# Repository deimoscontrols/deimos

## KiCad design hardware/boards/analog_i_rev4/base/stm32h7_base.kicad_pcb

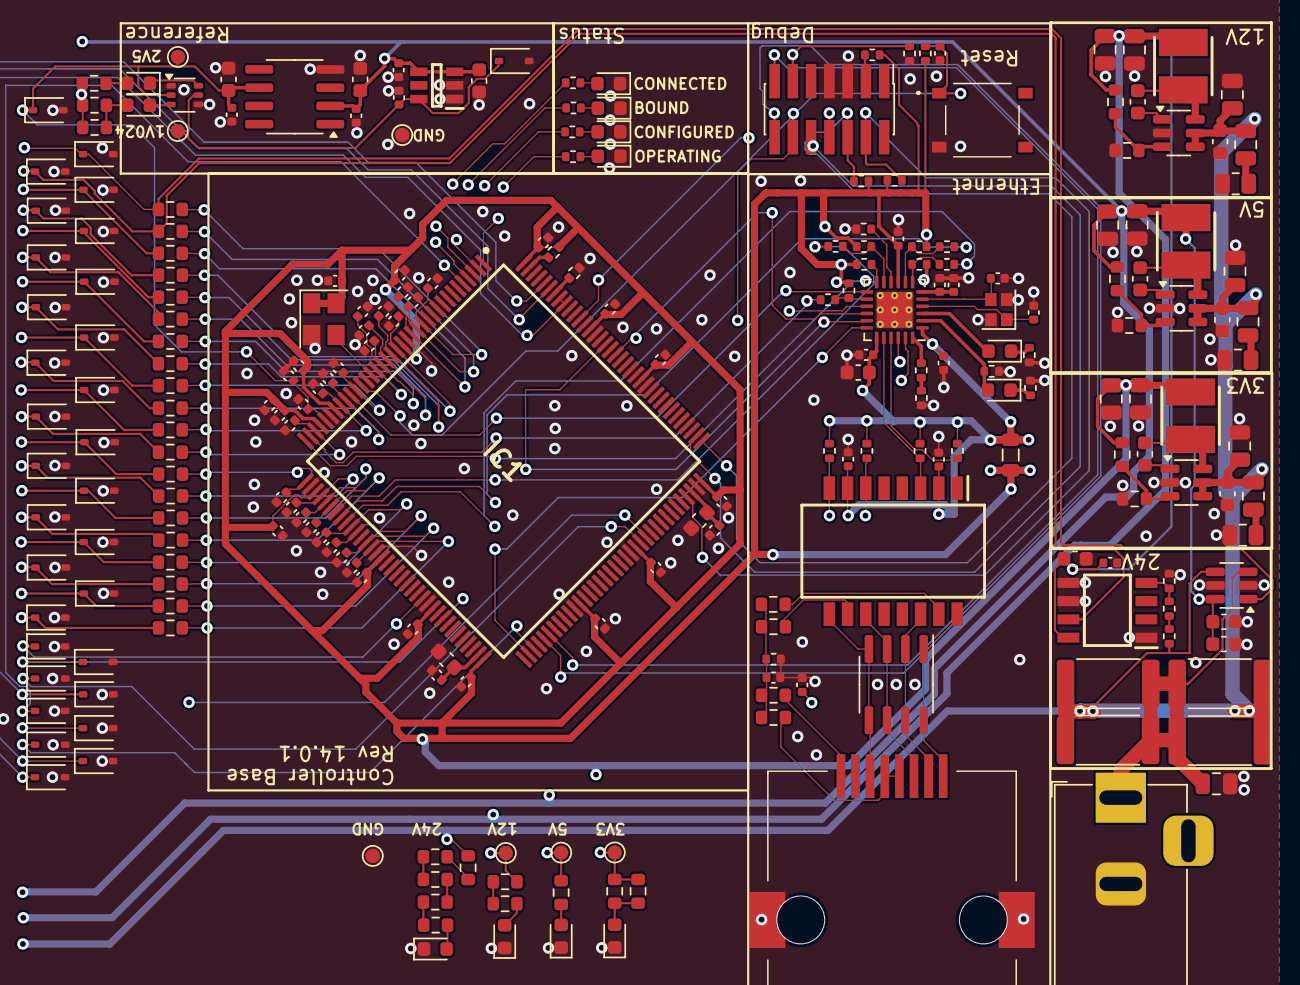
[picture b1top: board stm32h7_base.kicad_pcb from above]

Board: 4 copper layers, 242 parts (0 on the bottom side), 143 nets.

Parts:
C9, C10, C23, C4005, C5002, C5004, C6003: 10uF; C_0603_1608Metric
C11, C12, C13, C14, C15, C17, C18, C19, C22, C24, C26, C28, C29, C30, C31, C32, C33, C34, C35, C36, C37, C38, C39, C40, C4004, C5001, C5003, C6001, C6002: 0.1uF; C_0402_1005Metric
C16: 4.7nF; C_0402_1005Metric
C20, C21: 5.6pF 0402; C_0402_1005Metric
C25: 470pF 0402; C_0402_1005Metric
C27, C44, C45, C46, C47, C48, C49, C50, C51, C52, C53, C54, C55, C56, C57, C58, C59, C60, C61, C62, C63: 1uF 0402; C_0402_1005Metric
C42, C43: 10nF; C_0402_1005Metric
C4001: 0.1uF 0603; C_0603_1608Metric
C4002: 10uF 0603; C_0603_1608Metric
C4003, C7001, C7002, C7004, C8003, C9004, C11005, C11006, C12002, C12003: 10uF 50V 0805; C_0805_2012Metric
C7003, C8001, C9001, C9002, C10005, C11009: 0.1uF 50V 0603; C_0603_1608Metric
C8002, C9003, C10006: 2.2uF 50V 0805; C_0805_2012Metric
D2, D6, D36, D37, D38, D39, D7004, D7005, D7006, D7007, D7008, D7009: Purple LED; LED_0603_1608Metric
D5: CDNBS08-SLVU2.8-4; SOIC-8_3.9x4.9mm_P1.27mm
D7, D1001, D1002, D1003, D1004, D1005, D1006, D1007, D1008, D1009, D1010, D1011, D1012, D1013, D1014, D1015, D1016, D1017, D1018, D1019, D1020, D1021, D1022, D1023, D1024, D1025, D1026, D1027, D1028, D1029, D1030: BZT52C5V6S; D_SOD-323
FB1: GZ2012D601TF; L_0805_2012Metric
H1001, H1002: MountingHole_for_10-32; MountingHole_5mm
IC1: STM32H743ZIT6; QFP50P2200X2200X160-144N
IC5004: REF35102QDBVR; SOT95P280X145-6N
IC8001: INA826AIDR; SOIC127P600X175-8N
IC8002, IC10001, IC12001: TPS560430XDBVR; SOT-23-6
J4: Conn_02x07_Odd_Even; PinHeader_2x07_P1.27mm_Vertical_SMD
J7: 6339160-1; 63391601
J8001: Barrel_Jack; BarrelJack_Horizontal
L7001: 12uH FNR4030S120MT; INDPM4040X300N
L9001: 33uH FNR4020S330MT; INDPM4040X300N
L11001: 18uH FNR4030S180MT; INDPM4040X300N
R1, R2, R3, R4, R5, R6, R27, R28, R29, R30, R31, R33, R49, R50, R53, R55, R8006, R8007: 10k; R_0402_1005Metric
R8, R9, R10, R11, R22, R32, R35, R36, R37, R38, R39, R40, R41, R42, R43, R44, R45, R46, R51, R52: 10R 0603; R_0603_1608Metric
R13, R14, R15, R16: 49.9; R_0402_1005Metric
R17, R18, R19, R20: 75; R_0603_1608Metric
R21: 1M; R_0402_1005Metric
R23, R26, R47, R48: 33R; R_0402_1005Metric
R34, R56, R8005: 1.5k; R_0402_1005Metric
R54: 12k; R_0402_1005Metric
R57: 100R; R_0402_1005Metric
R58, R2001: 100R 0402; R_0402_1005Metric
R4001, R4002, R4003, R8004: MRF6432(2512)LR030FTS 0.030 1%; R_2512_6332Metric
R7001: 51k 0603; R_0603_1608Metric
R7025, R7026, R7027, R7028, R7029, R7030, R7031, R7033, R7034, R10002, R10004, R10005, R10006: 10k; R_0603_1608Metric
R9001: 243k 0603; R_0603_1608Metric
R9002, R10001, R11004: 22.1k 0603; R_0603_1608Metric
R10003, R11005, R12003: 1R 0805; R_0805_2012Metric
R11003: 88.7k 0603; R_0603_1608Metric
S1: TS-1187A-B-A-B; TS1187ABAB
T1: H1102NLT; SOIC127P940X622-16N
TP4001: TestPoint_GND_1; TestPoint_Pad_D1.0mm
TP10001: TestPoint_+12V; TestPoint_Pad_D1.0mm
TP10002: TestPoint_+5V; TestPoint_Pad_D1.0mm
TP10003: TestPoint_+2V5; TestPoint_Pad_D1.0mm
TP10004: TestPoint_+3V3; TestPoint_Pad_D1.0mm
TP10005: TestPoint_+1V024; TestPoint_Pad_D1.0mm
TP10006: TestPoint_GND; TestPoint_Pad_D1.0mm
U5: LAN8742A; VQFN-24-1EP_4x4mm_P0.5mm_EP2.5x2.5mm_ThermalVias
U4001: INA181A2; SOT-23-6
U6002: ADR4525; SOIC-8_3.9x4.9mm_P1.27mm
U10001: NTJD4001NT1G; SOT-363_SC-70-6
Y1: SiT1602BI-21-33S-48.000000; Crystal_SMD_3225-4Pin_3.2x2.5mm
Y2: NX2016SA-25.000M-STD-CZS-1; Crystal_SMD_2016-4Pin_2.0x1.6mm

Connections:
+1V024: C6001.2, D1030.1 (K), IC5004.6 (VREF), TP10005.1, U10001.5 (G2)
+2V5: C28.2, C43.2, C5003.2, C5004.2, D1028.1 (K), IC1.32 (VREF+), TP10003.1, U6002.6 (OUT), U10001.2 (G1)
+3V3: C11.2, C12.2, C26.2, C29.2, C30.2, C31.2, C32.2, C33.2, C34.2, C35.2, C36.2, C37.2, C38.2, C39.2, C40.2, C42.2, C7004.1, C10006.1, FB1.1, IC1.17 (VDD_1), IC1.30 (VDD_2), IC1.33 (VDDA), IC1.39 (VDD_3), IC1.52 (VDD_4), IC1.62 (VDD_5), IC1.72 (VDD_6), IC1.84 (VDD_7), IC1.95 (VDD33USB), IC1.108 (VDD_8), IC1.121 (VDD_9), IC1.131 (VDD_10), IC1.144 (VDD_11), L7001.1, R1.2, R2.1, R3.2, R6.1, R27.1, R28.1, R29.1, R49.1, R56.2, R2001.1, R7001.1, R7031.2, R10002.2, TP10004.1, U5.9 (VDDIO), Y1.1 (OE/~ST/NC), Y1.4 (VDD)
+5V: C4001.1, C4002.1, C5001.2, C5002.2, C6002.2, C6003.2, C8002.1, C8003.1, IC5004.3 (EN), IC5004.4 (VIN), L11001.1, R7029.2, R7030.2, R10004.2, R10005.2, R11003.1, TP10002.1, U4001.6 (V+), U6002.2 (IN)
+12V: C4004.2, C4005.2, C9003.1, C9004.1, IC8001.8 (+VS), L9001.1, R7027.2, R9001.1, TP10001.1
+24V: C7001.1, C7002.1, C8001.1, C9001.1, C10005.1, C11005.1, C11006.1, C12002.1, C12003.1, IC8002.4 (EN), IC8002.5 (VIN), IC10001.4 (EN), IC10001.5 (VIN), IC12001.4 (EN), IC12001.5 (VIN), R4001.1, R4002.1, R4003.1, R8004.1, R8006.1, R10006.2, U4001.4 (-)
/AIN0: D7.1 (K), R8.1, U4001.1
/AIN1: D1001.1 (K), IC8001.7 (VOUT), R9.1
/AIN2: D1002.1 (K), R10.1
/AIN3: D1003.1 (K), R11.1
/AIN4: D1004.1 (K), R22.1
/AIN5: D1005.1 (K), R32.1
/AIN6: D1006.1 (K), R35.1
/AIN7: D1007.1 (K), R36.1
/AIN8: D1008.1 (K), R37.1
/AIN9: D1009.1 (K), R38.1
/AIN10: D1010.1 (K), R39.1
/AIN11: D1011.1 (K), R40.1
/AIN12: D1012.1 (K), R41.1
/AIN13: D1013.1 (K), R42.1
/AIN14: D1014.1 (K), R43.1
/AIN15: D1015.1 (K), R44.1
/AIN16: D1016.1 (K), R45.1
/AIN17: D1017.1 (K), R46.1
/AIN18: D1018.1 (K), R51.1
/AIN19: D1019.1 (K), R52.1
/COUNTER0: D1025.1 (K), IC1.96 (PC6)
/ENCODER0_0: D1020.1 (K), IC1.60 (PE9)
/ENCODER0_1: D1029.1 (K), IC1.64 (PE11)
/FREQ0: D1026.1 (K), IC1.136 (PB6), IC1.137 (PB7)
/FREQ1: D1027.1 (K), IC1.5 (PE6)
/Micro/AIN0_Filt: C44.1, IC1.13 (PF3), R8.2
/Micro/AIN1_Filt: C45.1, IC1.14 (PF4), R9.2
/Micro/AIN2_Filt: C46.1, IC1.15 (PF5), R10.2
/Micro/AIN3_Filt: C47.1, IC1.18 (PF6), R11.2
/Micro/AIN4_Filt: C48.1, IC1.19 (PF7), R22.2
/Micro/AIN5_Filt: C49.1, IC1.20 (PF8), R32.2
/Micro/AIN6_Filt: C50.1, IC1.21 (PF9), R35.2
/Micro/AIN7_Filt: C51.1, IC1.22 (PF10), R36.2
/Micro/AIN8_Filt: C52.1, IC1.26 (PC0), R37.2
/Micro/AIN9_Filt: C53.1, IC1.28 (PC2_C), R38.2
/Micro/AIN10_Filt: C54.1, IC1.29 (PC3_C), R39.2
/Micro/AIN11_Filt: C55.1, IC1.34 (PA0), R40.2
/Micro/AIN12_Filt: C56.1, IC1.37 (PA3), R41.2
/Micro/AIN13_Filt: C57.1, IC1.40 (PA4), R42.2
/Micro/AIN14_Filt: C58.1, IC1.41 (PA5), R43.2
/Micro/AIN15_Filt: C59.1, IC1.42 (PA6), R44.2
/Micro/AIN16_Filt: C60.1, IC1.46 (PB0), R45.2
/Micro/AIN17_Filt: C61.1, IC1.47 (PB1), R46.2
/Micro/AIN18_Filt: C62.1, IC1.49 (PF11), R51.2
/Micro/AIN19_Filt: C63.1, IC1.50 (PF12), R52.2
/Micro/DEBUG_RESET: C19.2, IC1.25 (NRST), J4.12, R2.2, S1.A1 (COM_1), U5.15 (~RST)
/Micro/DEBUG_TCK/SWCLK: IC1.109 (PA14), J4.6, R1.1
/Micro/DEBUG_TDI: IC1.110 (PA15), J4.10
/Micro/DEBUG_TDO/SWO: IC1.133 (PB3), J4.8
/Micro/DEBUG_TMS/SWDIO: IC1.105 (PA13), J4.4, R3.1
/Micro/Ethernet/RX+: R14.1, T1.6 (RD+), U5.23 (RXP)
/Micro/Ethernet/RX-: R13.1, T1.8 (RD-), U5.22 (RXN)
/Micro/Ethernet/TX+: R16.1, T1.1 (TD+), U5.21 (TXP)
/Micro/Ethernet/TX-: R15.1, T1.3 (TD-), U5.20 (TXN)
/Micro/HSECLK: IC1.23 (PH0-OSC_IN), Y1.3 (OUT)
/Micro/LED0: IC1.4 (PE5), R55.2
/Micro/LED1: IC1.3 (PE4), R5.2
/Micro/LED2: IC1.2 (PE3), R50.2
/Micro/LED3: IC1.1 (PE2), R53.2
/Micro/RMII_CRS_DV: IC1.43 (PA7), R47.1
/Micro/RMII_MDC: IC1.27 (PC1), U5.13 (MDC)
/Micro/RMII_MDIO: IC1.36 (PA2), R56.1, U5.12 (MDIO)
/Micro/RMII_REF_CLK: IC1.35 (PA1), R48.2
/Micro/RMII_RXD0: IC1.44 (PC4), R26.2
/Micro/RMII_RXD1: IC1.45 (PC5), R23.2
/Micro/RMII_TXD0: IC1.128 (PG13), U5.17 (TXD0)
/Micro/RMII_TXD1: IC1.74 (PB13), U5.18 (TXD1)
/Micro/RMII_TX_EN: IC1.126 (PG11), U5.16 (TXEN)
/Micro/UART_RX: IC1.78 (PD9), J4.13
/Micro/UART_TX: IC1.77 (PD8), J4.14
/PWM0: D1021.1 (K), IC1.97 (PC7)
/PWM1: D1022.1 (K), IC1.75 (PB14)
/PWM2: D1023.1 (K), IC1.139 (PB8)
/PWM3: D1024.1 (K), IC1.140 (PB9)
GND: C9.1, C10.2, C11.1, C12.1, C13.1, C14.1, C15.1, C16.2, C17.1, C18.1, C19.1, C20.1, C21.1, C22.1, C23.1, C24.1, C25.1, C26.1, C27.1, C28.1, C29.1, C30.1, C31.1, C32.1, C33.1, C34.1, C35.1, C36.1, C37.1, C38.1, C39.1, C40.1, C42.1, C43.1, C44.2, C45.2, C46.2, C47.2, C48.2, C49.2, C50.2, C51.2, C52.2, C53.2, C54.2, C55.2, C56.2, C57.2, C58.2, C59.2, C60.2, C61.2, C62.2, C63.2, C4001.2, C4002.2, C4003.2, C4004.1, C4005.1, C5001.1, C5002.1, C5003.1, C5004.1, C6001.1, C6002.1, C6003.1, C7002.2, C7004.2, C8001.2, C8002.2, C8003.2, C9001.2, C9003.2, C9004.2, C10005.2, C10006.2, C11006.2, C12003.2, D6.1 (K), D7.2 (A), D37.1 (K), D38.1 (K), D39.1 (K), D1001.2 (A), D1002.2 (A), D1003.2 (A), D1004.2 (A), D1005.2 (A), D1006.2 (A), D1007.2 (A), D1008.2 (A), D1009.2 (A), D1010.2 (A), D1011.2 (A), D1012.2 (A), D1013.2 (A), D1014.2 (A), D1015.2 (A), D1016.2 (A), D1017.2 (A), D1018.2 (A), D1019.2 (A), D1020.2 (A), D1021.2 (A), D1022.2 (A), D1023.2 (A), D1024.2 (A), D1025.2 (A), D1026.2 (A), D1027.2 (A), D1028.2 (A), D1029.2 (A), D1030.2 (A), D7006.1 (K), D7007.1 (K), D7008.1 (K), D7009.1 (K), IC1.16 (VSS_1), IC1.31 (VSSA), IC1.38 (VSS_2), IC1.51 (VSS_3), IC1.61 (VSS_4), IC1.83 (VSS_5), IC1.94 (VSS_6), IC1.107 (VSS_7), IC1.120 (VSS_8), IC1.130 (VSS_9), IC5004.1 (GND_1), IC5004.2 (GND_2), IC8001.1 (-IN1), IC8001.5 (-VS), IC8001.6 (REF), IC8002.2 (GND), IC10001.2 (GND), IC12001.2 (GND), J4.5, J4.7, J7.9, J7.10, J8001.2, R4.2, R21.2, R30.1, R31.2, R33.2, R34.1, R57.1, R58.1, R8005.1, R9002.2, R10001.2, R10003.2, R11004.2, R11005.2, R12003.2, S1.C1 (NO_1), TP4001.1, TP10006.1, U5.25 (VSS), U4001.2 (GND), U4001.5 (REF), U6002.4 (GND), U10001.1 (S1), U10001.4 (S2), Y1.2 (GND), Y2.2 (GND_1), Y2.4 (GND_2)
unnamed: C16.1, R17.2, R18.1, R19.1, R20.2, R21.1
unnamed: C7001.2, R10003.1
unnamed: C11005.2, R11005.1
unnamed: C12002.2, R12003.1
unnamed: D2.2 (A), U5.3 (LED1/REGOFF)
unnamed: D2.1 (K), R31.1
unnamed: D6.2 (A), R5.1
unnamed: D36.2 (A), R33.1, U5.2 (LED2/~INTSEL)
unnamed: D36.1 (K), R34.2
unnamed: D37.2 (A), R50.1
unnamed: D38.2 (A), R53.1
unnamed: D39.2 (A), R55.1
unnamed: D7004.2 (A), R7029.1
unnamed: D7004.1 (K), U10001.6 (D1)
unnamed: D7005.2 (A), R7030.1, R10004.1
unnamed: D7005.1 (K), U10001.3 (D2)
unnamed: D7006.2 (A), R7031.1, R10002.1
unnamed: D7007.2 (A), R10005.1
unnamed: D7008.2 (A), R7033.1
unnamed: D7009.2 (A), R7034.1
unnamed: IC1.138 (BOOT0), R4.1
unnamed: IC1.143 (PDR_ON), R6.2
unnamed: C9.2, C18.2, IC1.71 (VCAP_1)
unnamed: C10.1, C17.2, IC1.106 (VCAP_2)
unnamed: IC8001.4 (+IN), R8005.2, R8007.1
unnamed: C11009.2, IC8002.1 (CB)
unnamed: IC8002.3 (FB), R11003.2, R11004.1
unnamed: C11009.1, IC8002.6 (SW), L11001.2
unnamed: C7003.2, IC10001.1 (CB)
unnamed: IC10001.3 (FB), R7001.2, R10001.1
unnamed: C7003.1, IC10001.6 (SW), L7001.2
unnamed: C9002.2, IC12001.1 (CB)
unnamed: IC12001.3 (FB), R9001.2, R9002.1
unnamed: C9002.1, IC12001.6 (SW), L9001.2
unnamed: J4.3, R2001.2
unnamed: J4.11, R58.2
unnamed: J7.4, J7.5, R19.2
unnamed: J7.7, J7.8, R20.1
unnamed: R54.1, R57.2
unnamed: R7025.1, R7033.2
unnamed: R7025.2, R7026.1
unnamed: R7026.2, R7028.1
unnamed: R7027.1, R7034.2
unnamed: R8006.2, R8007.2
unnamed: R7028.2, R10006.1
unnamed: C13.2, C14.2, C15.2, C22.2, C23.2, C24.2, FB1.2, R13.2, R14.2, R15.2, R16.2, T1.2 (CT_1), T1.7 (CT_2), U5.1 (VDD2A), U5.19 (VDD1A)
unnamed: R17.1, T1.10 (NC_3)
unnamed: R18.2, T1.15 (NC_6)
unnamed: D5.3 (TVS1), D5.6 (TVS2), J7.3, T1.11 (RX+)
unnamed: D5.4 (TVS2), D5.5 (TVS1), J7.6, T1.9 (RX-)
unnamed: D5.1 (TVS1), D5.8 (TVS2), J7.1, T1.16 (TX+)
unnamed: D5.2 (TVS2), D5.7 (TVS1), J7.2, T1.14 (TX-)
unnamed: R28.2, R47.2, U5.11 (CRS_DV/MODE2)
unnamed: R54.2, U5.24 (RBIAS)
unnamed: R26.1, R49.2, U5.8 (RXD0/MODE0)
unnamed: R23.1, R27.2, U5.7 (RXD1/MODE1)
unnamed: R30.2, U5.10 (RXER/PHYAD0)
unnamed: C25.2, C27.2, U5.6 (VDDCR)
unnamed: C20.2, U5.5 (XTAL1/CLKIN), Y2.3 (CRYSTAL_2)
unnamed: C21.2, U5.4 (XTAL2), Y2.1 (CRYSTAL_1)
unnamed: R29.2, R48.1, U5.14 (~INT/REFCLKO)
unnamed: C4003.1, J8001.1, R4001.2, R4002.2, R4003.2, R8004.2, U4001.3 (+)
